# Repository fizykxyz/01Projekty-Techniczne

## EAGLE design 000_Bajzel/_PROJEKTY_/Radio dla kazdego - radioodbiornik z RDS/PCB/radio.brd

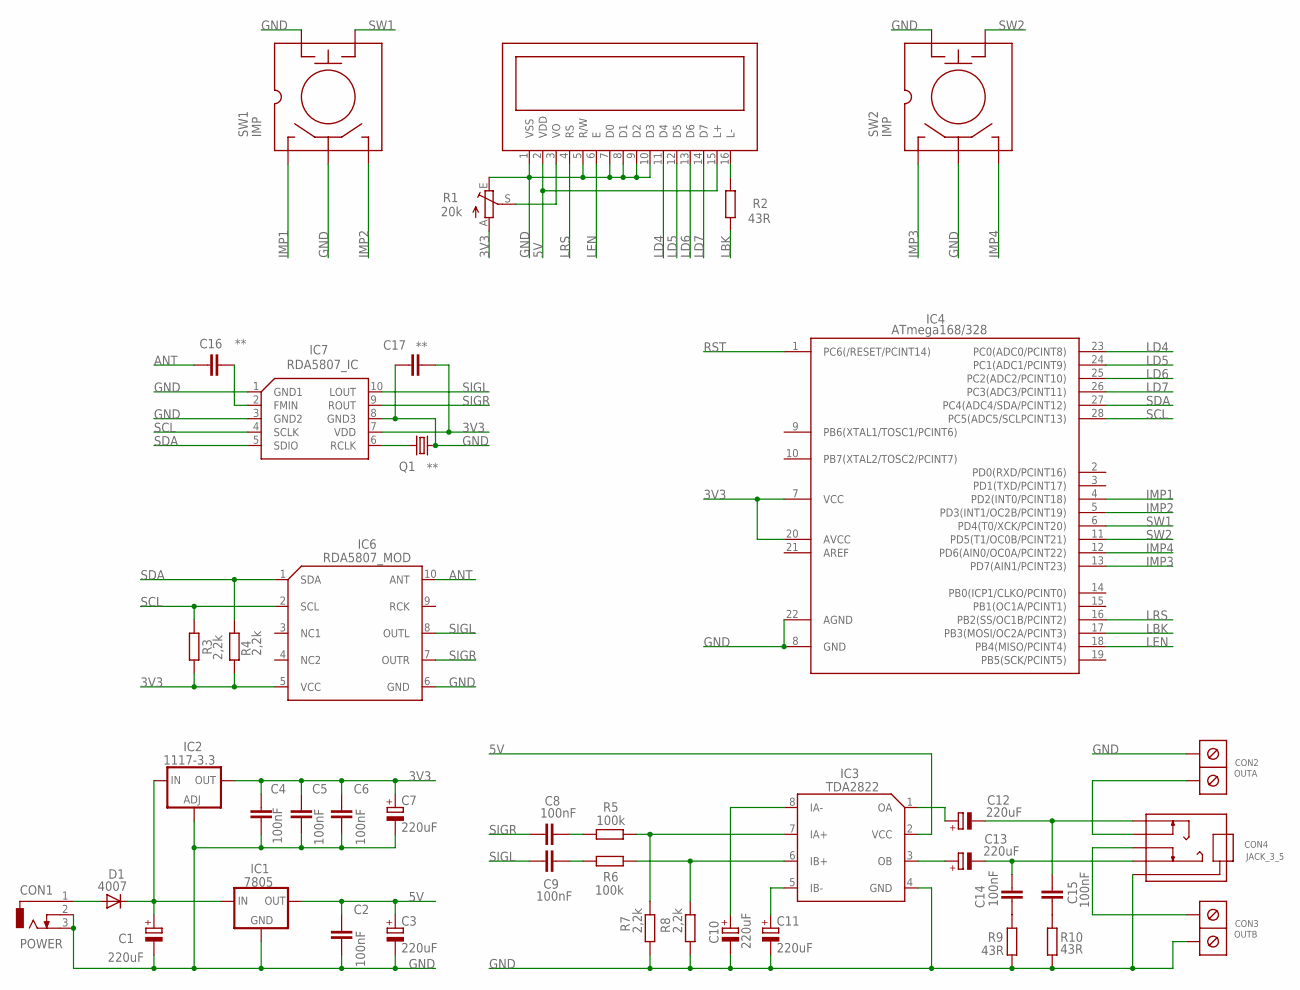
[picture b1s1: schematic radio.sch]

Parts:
C1, C3, C7, C10, C11, C12, C13: 220uF; E2,5-7
C2, C4, C5, C6, C8, C9, C14, C15: 100nF; C050-030X075
C16, C17: **; C0805K
CON1: POWER; DCJ0202
CON2: OUTA; ARK2/300
CON3: OUTB; ARK2/300
CON4: JACK_3_5
D1: 4007; DO41-10
IC1: 7805; 78XXS
IC2: 1117-3.3; 317TS
IC3: TDA2822; DIL8
IC4: ATmega168/328; DIL28-3
IC5: LCD16X2
IC6: RDA5807_MOD
IC7: RDA5807_IC; MSOP10
Q1: **; TC38H
R1: 20k; CA6V
R2, R9, R10: 43R; 0207/7
R3, R4, R7, R8: 2,2k; 0207/7
R5, R6: 100k; 0207/7
SW1, SW2: IMP

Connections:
3V3: C4.1, C5.1, C6.1, C7.+, C17.2, IC2.2 (OUT), IC4.7 (VCC), IC4.20 (AVCC), IC6.5 (VCC), IC7.7 (VDD), R1.A, R3.2, R4.2
5V: C2.1, C3.+, IC1.OUT, IC3.2 (VCC), IC5.2 (VDD), IC5.15 (L+)
ANT: C16.1, IC6.10 (ANT)
GND: C1.-, C2.2, C3.-, C4.2, C5.2, C6.2, C7.-, C10.-, C11.-, C17.1, CON1.2, CON1.3, CON2.2, CON3.1, CON4.G, IC1.GND, IC2.1 (ADJ), IC3.4 (GND), IC4.8 (GND), IC4.22 (AGND), IC5.1 (VSS), IC5.5 (R/W), IC5.7 (D0), IC5.8 (D1), IC5.9 (D2), IC5.10 (D3), IC6.6 (GND), IC7.1 (GND1), IC7.3 (GND2), IC7.8 (GND3), Q1.1, R1.E, R7.2, R8.2, R9.2, R10.2, SW1.2, SW1.5, SW2.2, SW2.5
HL: C13.-, C14.2, CON4.L
HR: C12.-, C15.2, CON4.R
IMP1: IC4.4 (PD2(INT0/PCINT18)), SW1.1
IMP2: IC4.5 (PD3(INT1/OC2B/PCINT19)), SW1.3
IMP3: IC4.13 (PD7(AIN1/PCINT23)), SW2.1
IMP4: IC4.12 (PD6(AIN0/OC0A/PCINT22)), SW2.3
LBK: IC4.17 (PB3(MOSI/OC2A/PCINT3)), R2.1
LD4: IC4.23 (PC0(ADC0/PCINT8)), IC5.11 (D4)
LD5: IC4.24 (PC1(ADC1/PCINT9)), IC5.12 (D5)
LD6: IC4.25 (PC2(ADC2/PCINT10)), IC5.13 (D6)
LD7: IC4.26 (PC3(ADC3/PCINT11)), IC5.14 (D7)
LEN: IC4.18 (PB4(MISO/PCINT4)), IC5.6 (E)
LRS: IC4.16 (PB2(SS/OC1B/PCINT2)), IC5.4 (RS)
unnamed: C14.1, R9.1
unnamed: C15.1, R10.1
unnamed: IC5.3 (VO), R1.S
unnamed: CON2.1, CON4.RW
unnamed: C12.+, IC3.1 (OA)
unnamed: IC3.7 (IA+), R5.2, R7.1
unnamed: IC3.6 (IB+), R6.2, R8.1
unnamed: C11.+, IC3.5 (IB-)
unnamed: C10.+, IC3.8 (IA-)
unnamed: CON3.2, CON4.LW
unnamed: C9.2, R6.1
unnamed: C8.2, R5.1
unnamed: C13.+, IC3.3 (OB)
unnamed: C1.+, D1.C, IC1.IN, IC2.3 (IN)
unnamed: IC7.6 (RCLK), Q1.2
unnamed: CON1.1, D1.A
unnamed: C16.2, IC7.2 (FMIN)
unnamed: IC5.16 (L-), R2.2
RST: IC4.1 (PC6(/RESET/PCINT14))
SCL: IC4.28 (PC5(ADC5/SCLPCINT13)), IC6.2 (SCL), IC7.4 (SCLK), R3.1
SDA: IC4.27 (PC4(ADC4/SDA/PCINT12)), IC6.1 (SDA), IC7.5 (SDIO), R4.1
SIGL: C9.1, IC6.8 (OUTL), IC7.10 (LOUT)
SIGR: C8.1, IC6.7 (OUTR), IC7.9 (ROUT)
SW1: IC4.6 (PD4(T0/XCK/PCINT20)), SW1.4
SW2: IC4.11 (PD5(T1/OC0B/PCINT21)), SW2.4

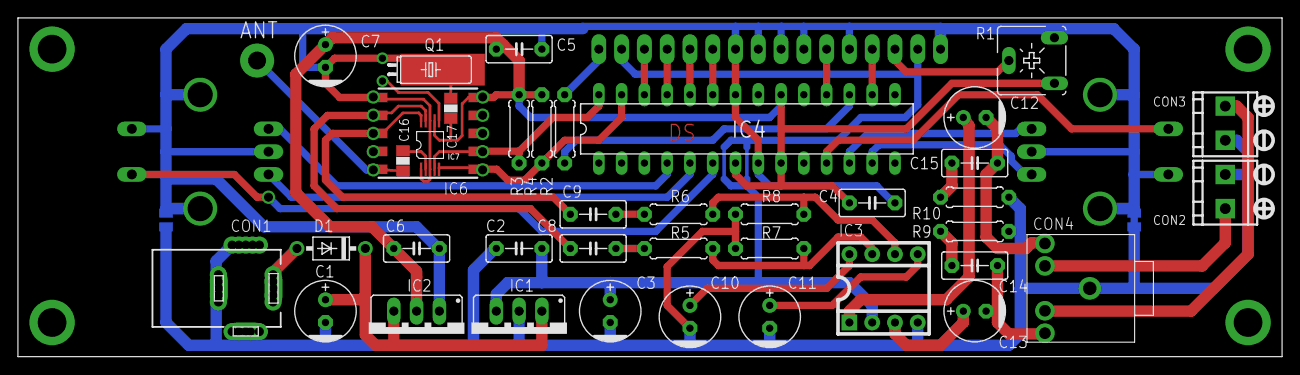
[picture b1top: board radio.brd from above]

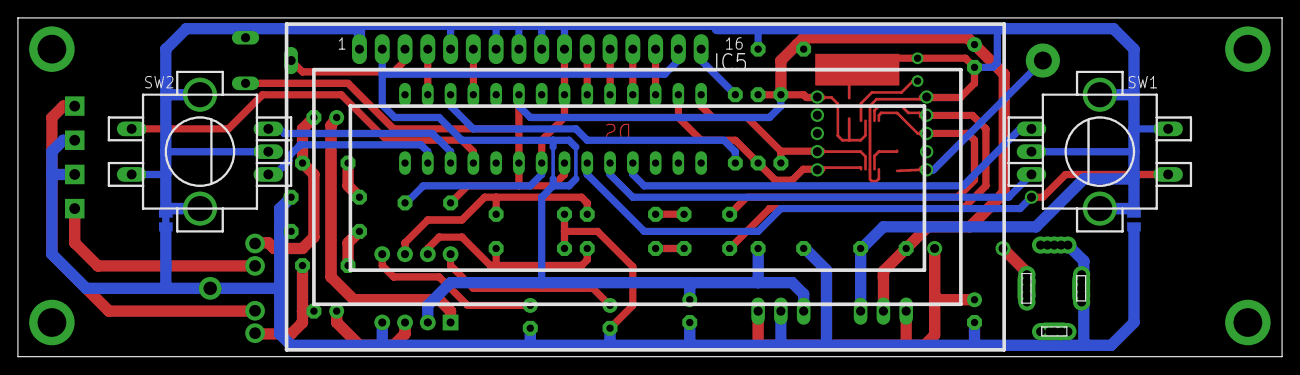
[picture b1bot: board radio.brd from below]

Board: 2 copper layers, 141.0 x 37.8 mm, 42 parts (3 on the bottom side), 41 nets.

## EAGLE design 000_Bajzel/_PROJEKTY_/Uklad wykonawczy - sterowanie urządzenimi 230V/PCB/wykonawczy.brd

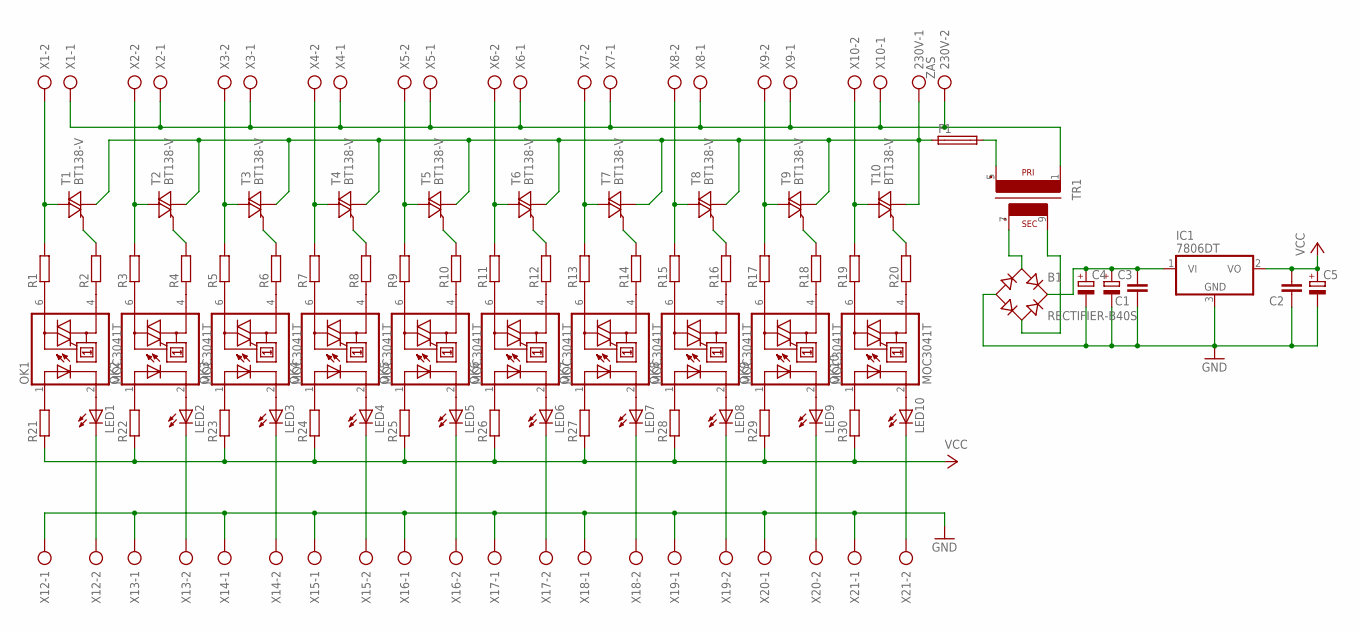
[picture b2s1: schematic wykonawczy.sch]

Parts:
230V: ZAS; AK500/2
B1: RECTIFIER-B40S; B40S
C1, C2: C-EU025-025X050; C025-025X050
C3, C4, C5: CPOL-EUE2.5-6; E2,5-6
F1: 19560
IC1: 7806DT; TO252
LED1, LED2, LED3, LED4, LED5, LED6, LED7, LED8, LED9, LED10: LED5MM
OK1, OK2, OK3, OK4, OK5, OK6, OK7, OK8, OK9, OK10: MOC3041T; DIL06B
R1, R2, R3, R4, R5, R6, R7, R8, R9, R10, R11, R12, R13, R14, R15, R16, R17, R18, R19, R20, R21, R22, R23, R24, R25, R26, R27, R28, R29, R30: R-EU_0204/7; 0204/7
T1, T2, T3, T4, T5, T6, T7, T8, T9, T10: BT138-V; TO220BV
TR1: EI30-1
X1, X2, X3, X4, X5, X6, X7, X8, X9, X10, X12, X13, X14, X15, X16, X17, X18, X19, X20, X21: AK500/2

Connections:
GND: B1.-, C1.1, C2.1, C3.-, C4.-, C5.-, IC1.3 (GND), X12.1, X13.1, X14.1, X15.1, X16.1, X17.1, X18.1, X19.1, X20.1, X21.1
unnamed: R2.2, T1.G
unnamed: OK1.4 (A1), R2.1
unnamed: OK2.4 (A1), R4.1
unnamed: R4.2, T2.G
unnamed: OK3.4 (A1), R6.1
unnamed: OK4.4 (A1), R8.1
unnamed: OK5.4 (A1), R10.1
unnamed: OK6.4 (A1), R12.1
unnamed: OK7.4 (A1), R14.1
unnamed: OK8.4 (A1), R16.1
unnamed: OK9.4 (A1), R18.1
unnamed: OK10.4 (A1), R20.1
unnamed: R6.2, T3.G
unnamed: R8.2, T4.G
unnamed: R10.2, T5.G
unnamed: R12.2, T6.G
unnamed: R14.2, T7.G
unnamed: R16.2, T8.G
unnamed: R18.2, T9.G
unnamed: R20.2, T10.G
unnamed: OK1.6 (A2), R1.1
unnamed: OK2.6 (A2), R3.1
unnamed: OK3.6 (A2), R5.1
unnamed: OK4.6 (A2), R7.1
unnamed: OK5.6 (A2), R9.1
unnamed: OK6.6 (A2), R11.1
unnamed: OK7.6 (A2), R13.1
unnamed: OK8.6 (A2), R15.1
unnamed: OK9.6 (A2), R17.1
unnamed: OK10.6 (A2), R19.1
unnamed: R1.2, T1.T2 (A2), X1.2
unnamed: R3.2, T2.T2 (A2), X2.2
unnamed: R5.2, T3.T2 (A2), X3.2
unnamed: R7.2, T4.T2 (A2), X4.2
unnamed: R9.2, T5.T2 (A2), X5.2
unnamed: R11.2, T6.T2 (A2), X6.2
unnamed: R13.2, T7.T2 (A2), X7.2
unnamed: R15.2, T8.T2 (A2), X8.2
unnamed: R17.2, T9.T2 (A2), X9.2
unnamed: R19.2, T10.T2 (A2), X10.2
unnamed: 230V.1, F1.1, T1.T1 (A1), T2.T1 (A1), T3.T1 (A1), T4.T1 (A1), T5.T1 (A1), T6.T1 (A1), T7.T1 (A1), T8.T1 (A1), T9.T1 (A1), T10.T1 (A1)
unnamed: F1.2, TR1.5 (P2)
unnamed: 230V.2, TR1.1, X1.1, X2.1, X3.1, X4.1, X5.1, X6.1, X7.1, X8.1, X9.1, X10.1
unnamed: B1.AC1, TR1.7 (S3)
unnamed: B1.AC2, TR1.9 (S4)
unnamed: B1.+, C1.2, C3.+, C4.+, IC1.1 (VI)
unnamed: OK1.1 (A), R21.2
unnamed: OK2.1 (A), R22.2
unnamed: OK3.1 (A), R23.2
unnamed: LED1.A, OK1.2 (C)
unnamed: LED2.A, OK2.2 (C)
unnamed: LED3.A, OK3.2 (C)
unnamed: LED4.A, OK4.2 (C)
unnamed: LED5.A, OK5.2 (C)
unnamed: LED6.A, OK6.2 (C)
unnamed: LED7.A, OK7.2 (C)
unnamed: LED8.A, OK8.2 (C)
unnamed: LED9.A, OK9.2 (C)
unnamed: LED10.A, OK10.2 (C)
unnamed: LED1.K (C), X12.2
unnamed: LED2.K (C), X13.2
unnamed: LED3.K (C), X14.2
unnamed: LED4.K (C), X15.2
unnamed: LED5.K (C), X16.2
unnamed: LED6.K (C), X17.2
unnamed: LED7.K (C), X18.2
unnamed: LED8.K (C), X19.2
unnamed: LED9.K (C), X20.2
unnamed: LED10.K (C), X21.2
unnamed: OK4.1 (A), R24.2
unnamed: OK5.1 (A), R25.2
unnamed: OK6.1 (A), R26.2
unnamed: OK7.1 (A), R27.2
unnamed: OK8.1 (A), R28.2
unnamed: OK9.1 (A), R29.2
unnamed: OK10.1 (A), R30.2
VCC: C2.2, C5.+, IC1.2 (VO), R21.1, R22.1, R23.1, R24.1, R25.1, R26.1, R27.1, R28.1, R29.1, R30.1

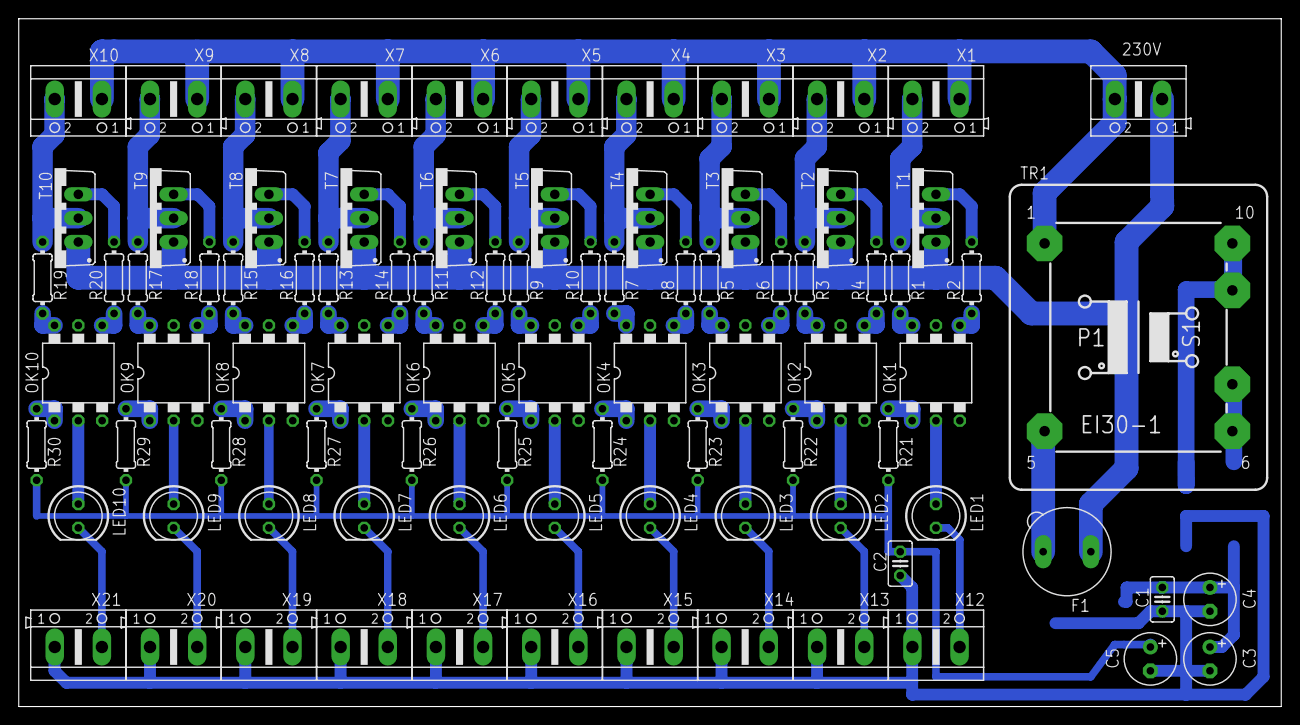
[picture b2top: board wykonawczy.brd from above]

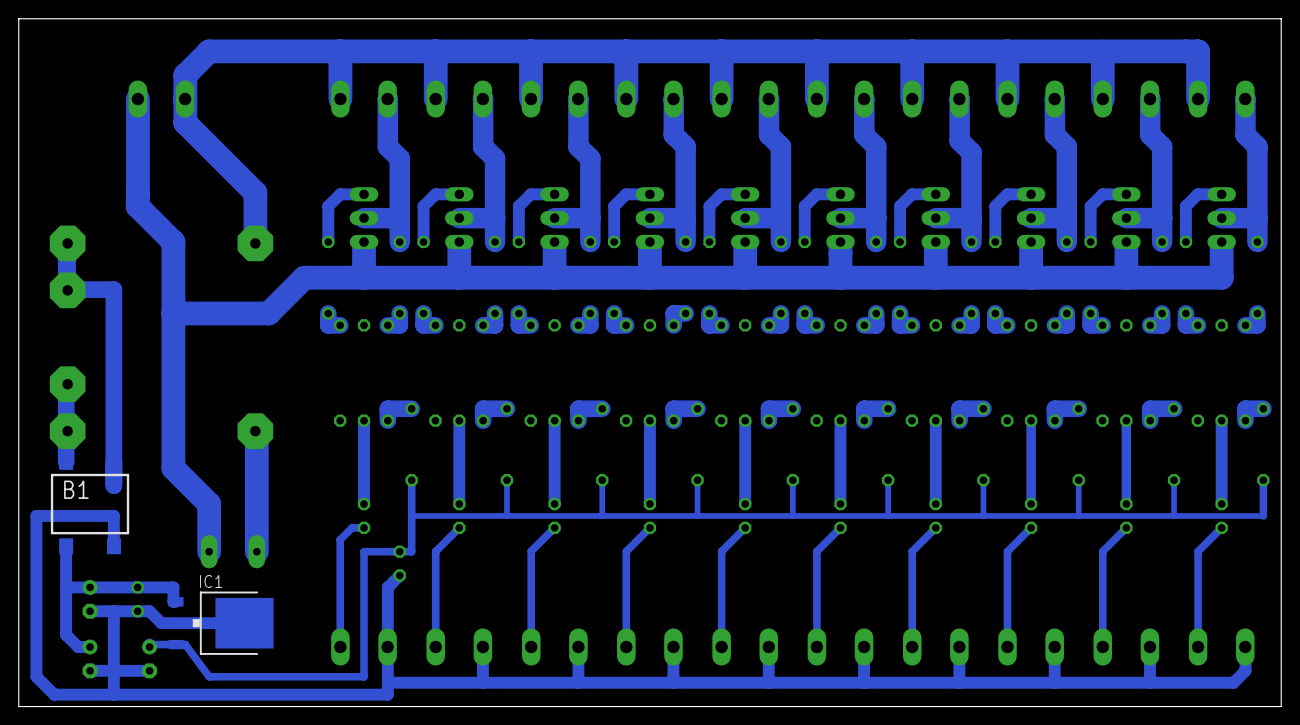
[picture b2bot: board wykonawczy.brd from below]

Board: 2 copper layers, 134.6 x 73.3 mm, 90 parts (2 on the bottom side), 78 nets.

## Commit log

2026-06-25 Inicjalizacja projektów: 001, 002... (Amiga Style)
2026-06-25 Aktualizacja projektów (001, 002...)
